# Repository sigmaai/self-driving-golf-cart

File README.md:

<center>

</center>

⚠️ This repo is no longer being maintained. Feel free to use the source or send me any questions, unfortunately no new commits or PRs will be added/accepted ⚠️

Welcome! This is an open source self-driving development platform aimed for rapid prototyping, deep learning, and robotics research. The system currently runs on a modified electric golf cart. Here are our goals:

### Goals:
Research and develop a deep learning-driven self-driving car. The vehicle should be able to achieve level 4 autonomy within a geofenced area.

#### The modules in this project.

1. End-to-End Steering (Behavioral cloning)
2. Semantic Segmentation
3. Object Detection 🚙
4. Drive by Wire (DBW)
5. CARLA simulator integration 
6. ZED stereoscopic vision system
7. Mapping with rtabamp
8. Path planning with ROS nav stack. 
9. Localization, pose tracking, and odom with ZED and rtabmap.

For the full documentation of the development process, please visit my website: [www.neilnie.com](https://www.neilnie.com)

## Table of Content
- [Try it out](#Try%20it%20out)
- [About ROS](./ros/README.md)
- [Simulation](#Simulation)
- [Autopilot & End-to-End Behavioral Cloning](./ros/src/autopilot/README.md)
- [Semantic Segmentation](./ros/src/segmentation/README.md)
- [The Navigation Stack](./ros/src/navigation/README.md)

## Try it out
Before you jump in, let me describe the hardware requirement for this project. **A webcam is the minimum requirment.** At this point, you can only run the whole system on the actual self-driving vehicle. ROS will throw warnings (even errors) at you if you don't have the hardware connected to your Linux machine. **If you don't have access to the hardware setup, don't worry** 👇
 
- The best way is to download and play back the ROS bags. [coming soon...]
- You can tryout individual packages and nodes, and might find them helpful for your own projects. 
- You can also tryout the CARLA simulator. (Maybe even improve the current system.)

To compile the project:

##### Requirements

1. Make sure that you have [ROS](http://wiki.ros.org/melodic/Installation/Ubuntu) installed on your computer. (I am using ROS Melodic)
2. Make sure you have all the [dependencies](./ros/requirements.txt) installed. 

##### Clone & Compile

1. Clone the repository. `$ git clone https://github.com/sigmaai/self-driving-golf-cart.git`
2. `$ cd self-driving-golf-cart/ros` 
3. `$ catkin_make`
4. `$ source devel/setup.bash`

##### Launch ZED cameras
- `$ roslaunch zed_wrapper zed.launch` (no rviz)
- `$ roslaunch zed_display display.launch` (with rviz)

##### Launch the Navigation Stack
- `$ roslaunch path_planning rtab_mapping_navigation.launch` 

<center>
	
</center>

🚙 Bon Voyage 😀

# Contact / Info
If you are interested in the detailed development process of this project, you can visit Neil's blog at [neilnie.com](https://neilnie.com) to find out more about it. Neil will make sure to keep you posted about all of the latest development on the club.

**Developers:**

**Neil (Yongyang) Nie** | [Email](mailto:yongyang.nie@gmail.com) | [Github](https://www.github.com/NeilNie) | [Website](neilnie.com) | [Linkedin](https://www.linkedin.com/in/yongyang-neil-nie-896204118/)

**Michael Meng** | [Email](mailto:xmeng18@deerfield.edu) | [Github](https://github.com/xmeng17)

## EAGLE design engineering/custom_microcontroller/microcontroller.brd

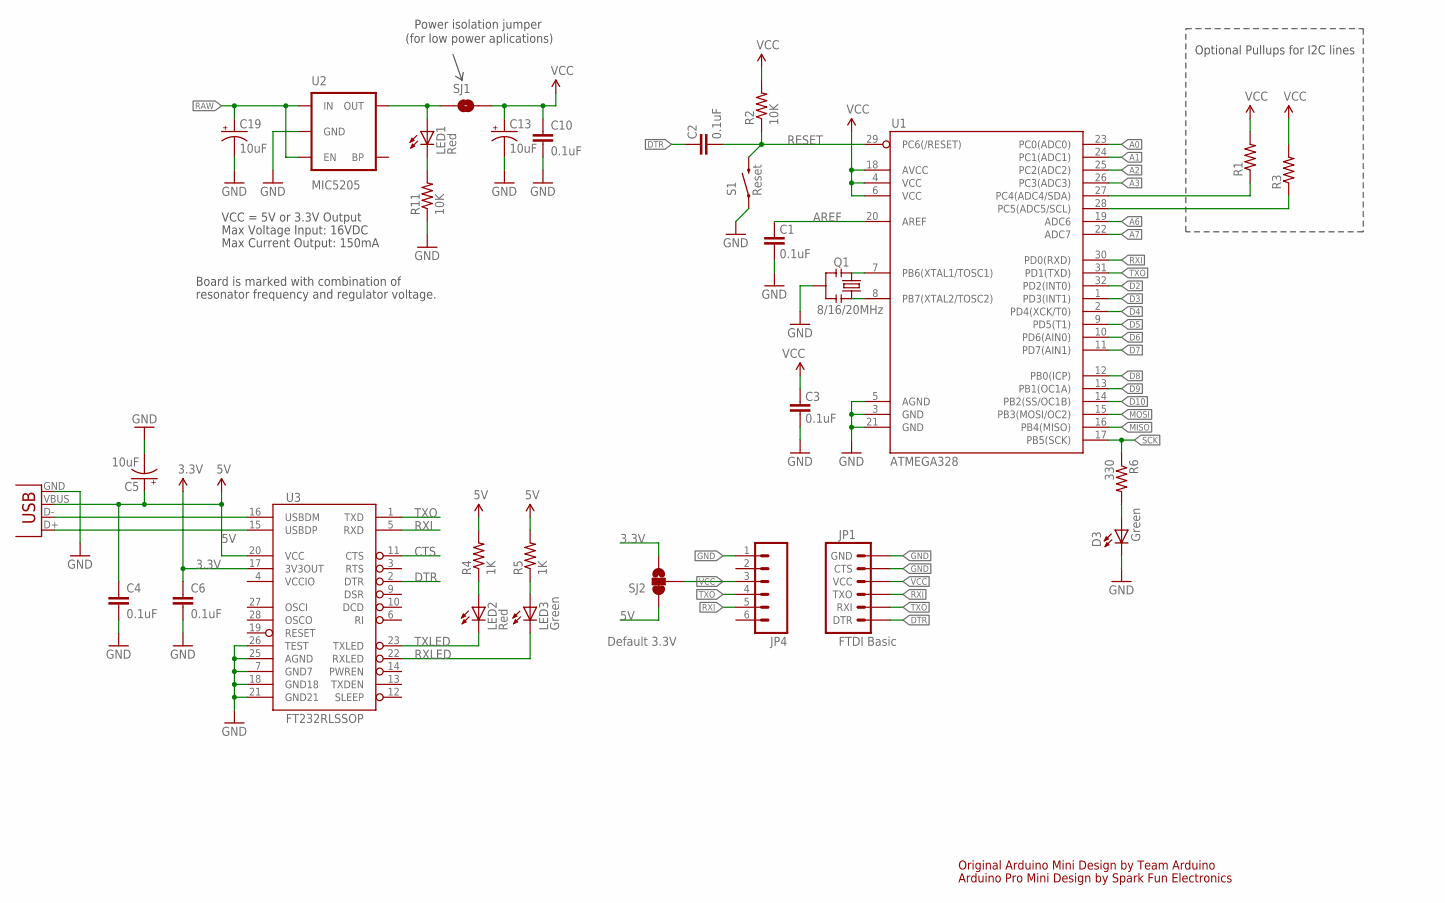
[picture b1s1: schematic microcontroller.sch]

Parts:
C1, C2, C3, C10: 0.1uF; 0603-CAP
C4, C6: 0.1uF; 0402-CAP
C5, C13, C19: 10uF; EIA3216
D3: Green; 0603-LED-ALT1
JP1: FTDI Basic; 1X06
JP4: M06SMD-FEMALE-V2; 1X06-SMD-FEMALE-V2
LED1: Red; 0603-LED-ALT1
LED2: Red; LED-0603
LED3: Green; LED-0603
Q1: 8/16/20MHz; RESONATOR-SMD-1:1
R1, R3: RESISTOR0603-RES; 0603-RES
R2, R11: 10K; 0603-RES
R4, R5: 1K; 0402-RES
R6: 330; 0603-RES
S1: Reset; TACTILE-SWITCH-SMD-ALT01
SJ1: SOLDERJUMPERNC; SJ_2S
SJ2: SOLDERJUMPER_2WAYS; SJ_3
U1: ATMEGA328; TQFP32-08
U2: MIC5205; SOT23-5
U3: FT232RLSSOP; SSOP28DB
X2: USB-SMD-NS; USB-MINIB-NOSTOP

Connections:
3.3V: C6.1, SJ2.3, U3.17 (3V3OUT)
5V: C4.1, C5.A (+), R4.2, R5.2, SJ2.1, U3.20 (VCC), X2.VBUS
A0: U1.23 (PC0(ADC0))
A1: U1.24 (PC1(ADC1))
A2: U1.25 (PC2(ADC2))
A3: U1.26 (PC3(ADC3))
A4: R1.1, U1.27 (PC4(ADC4/SDA)); also elsewhere on the board
A5: R3.1, U1.28 (PC5(ADC5/SCL)); also elsewhere on the board
A6: U1.19 (ADC6); also elsewhere on the board
A7: U1.22 (ADC7); also elsewhere on the board
AREF: C1.2, U1.20 (AREF)
CTS: JP4.2, U3.11 (CTS)
D2: U1.32 (PD2(INT0)); also elsewhere on the board
D3: U1.1 (PD3(INT1)); also elsewhere on the board
D4: U1.2 (PD4(XCK/T0)); also elsewhere on the board
D5: U1.9 (PD5(T1)); also elsewhere on the board
D6: U1.10 (PD6(AIN0)); also elsewhere on the board
D7: U1.11 (PD7(AIN1)); also elsewhere on the board
D8: U1.12 (PB0(ICP)); also elsewhere on the board
D9: U1.13 (PB1(OC1A)); also elsewhere on the board
D10: U1.14 (PB2(SS/OC1B))
DTR: C2.2, JP1.1 (DTR), JP4.6, U3.2 (DTR)
GND: C1.1, C3.1, C4.2, C5.C (-), C6.2, C10.2, C13.C (-), C19.C (-), D3.C, JP1.5 (CTS), JP1.6 (GND), JP4.1, Q1.2, R11.1, S1.1, S1.2 (1), U1.3 (GND), U1.5 (AGND), U1.21 (GND), U2.2 (GND), U3.7 (GND7), U3.18 (GND18), U3.21 (GND21), U3.25 (AGND), U3.26 (TEST), X2.GND; also elsewhere on the board
MISO: U1.16 (PB4(MISO))
MOSI: U1.15 (PB3(MOSI/OC2))
unnamed: Q1.3, U1.8 (PB7(XTAL2/TOSC2))
unnamed: Q1.1, U1.7 (PB6(XTAL1/TOSC1))
unnamed: LED1.A, SJ1.1, U2.5 (OUT)
unnamed: LED1.C, R11.2
unnamed: LED2.A, R4.1
unnamed: LED3.A, R5.1
unnamed: D3.A, R6.2
RAW: C19.A (+), U2.1 (IN), U2.3 (EN)
RXI: JP1.3 (TXO), JP4.5, U1.30 (PD0(RXD)), U3.5 (RXD); also elsewhere on the board
RXLED: LED3.C, U3.22 (RXLED)
SCK: R6.1, U1.17 (PB5(SCK))
TXLED: LED2.C, U3.23 (TXLED)
TXO: JP1.2 (RXI), JP4.4, U1.31 (PD1(TXD)), U3.1 (TXD); also elsewhere on the board
USB_D+: U3.15 (USBDP), X2.D+
USB_D-: U3.16 (USBDM), X2.D-
VCCIO: U3.4 (VCCIO)

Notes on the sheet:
Original Arduino Mini Design by Team Arduino
Arduino Pro Mini Design by Spark Fun Electronics
Max Voltage Input: 16VDC
Max Current Output: 150mA
Board is marked with combination of
resonator frequency and regulator voltage.
VCC = 5V or 3.3V Output
Optional Pullups for I2C lines
Power isolation jumper
(for low power aplications)
Default 3.3V

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
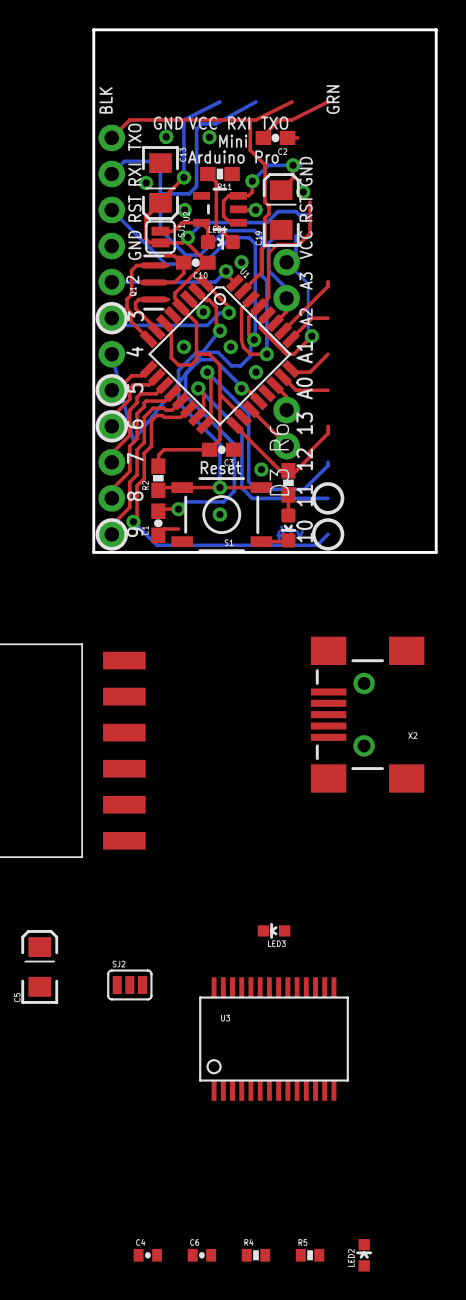
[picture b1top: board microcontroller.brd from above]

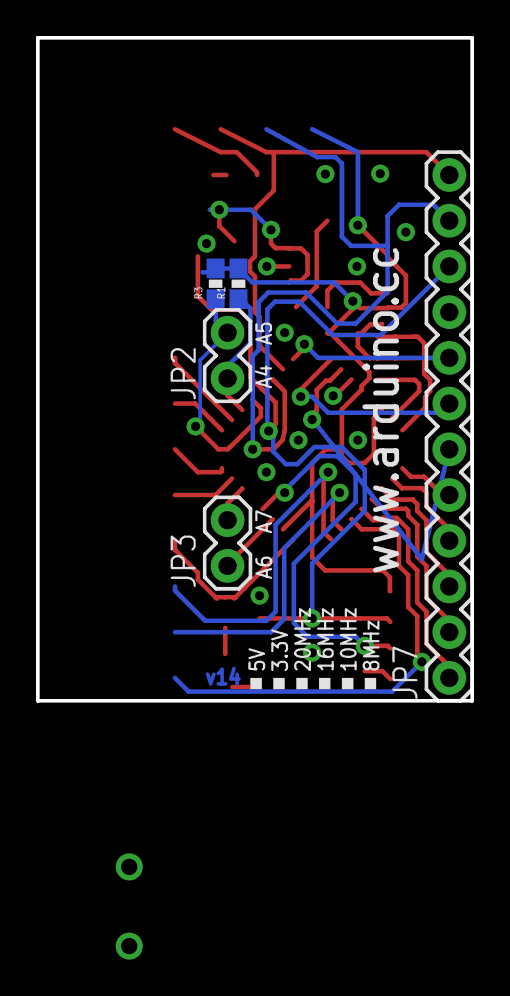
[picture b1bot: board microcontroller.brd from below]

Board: 2 copper layers, 24.1 x 36.8 mm, 32 parts (5 on the bottom side), 36 nets.

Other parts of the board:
JP2, JP3: 1X02
JP7: 1X12

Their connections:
A4: JP2.1; also elsewhere on the board
A5: JP2.2; also elsewhere on the board
A6: JP3.1; also elsewhere on the board
A7: JP3.2; also elsewhere on the board
D2: JP7.8; also elsewhere on the board
D3: JP7.7; also elsewhere on the board
D4: JP7.6; also elsewhere on the board
D5: JP7.5; also elsewhere on the board
D6: JP7.4; also elsewhere on the board
D7: JP7.3; also elsewhere on the board
D8: JP7.2; also elsewhere on the board
D9: JP7.1; also elsewhere on the board
GND: JP7.9; also elsewhere on the board
RXI: JP7.11; also elsewhere on the board
TXO: JP7.12; also elsewhere on the board

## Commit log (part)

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2017-10-25 newly trained files
2017-10-27 new error function added
2017-10-30 directory changed & small changes
2017-10-31 steering training modifications
2017-11-01 merging method finished
2017-11-04 attempted to make vechicle detection work
2017-11-09 ready for training uolo
2017-11-16 engineering files added & egpu set completed
2017-11-21 segmatation keras training improvements
2017-11-29 directory changed
2017-12-01 steering visualization works, lane detection added, traffic signal added
2017-12-03 servo code 'actually' added
2017-12-08 google maps & segmentation works
2017-12-20 MultiNet removed, begin implementing SegNet
2017-12-23 cruse added & other small changes
2018-01-06 round steering angle
2018-01-09 update arduino
2018-01-09 add case if does not get message
2018-01-10 motor integration
2018-01-12 fixed state
2018-01-14 schematics & engineering
2018-01-17 used new motor controller to handle higher amp
2018-01-23 cruse control code added
    - arduino serial python code added
    - speed predictor class added
    Note: need more training
    (same with steering)
2018-01-24 added two way communications
2018-01-25 cruse & steering training files changes
2018-01-30 latest training changes
2018-01-31 spelling error corrected
2018-02-05 small changes
2018-02-08 many changes
    - segmentation comfirmed to be working
    - segmentation visualization file updated
    - segmentation integrated into drive.py
    - drive.py detector stuff removed
    - vehicle detector dir removed
    - changed printing color for drive.py
2018-02-09 latest changes to be pushed to cart
2018-02-11 small changes
    pretty much meaningless
2018-02-14 small changes on cruise control
2018-02-20 arduino code updated, ready for some testing
2018-02-23 changes on cart
2018-02-25 tried rambo, didn't really work
2018-02-26 AutoPilot added, see if it works.
2018-03-01 multi-camera implemented & other small changes
2018-03-02 readme and other small changes
2018-03-06 data set collector implementations
2018-03-08 Updated license
2018-03-25 small changes & data set preprocessing
2018-04-05 detection stuff added 🚘
    - Yolo v2 added (again)
    - Lane detector added
    - traffic light detector added
2018-04-08 updated README
    and other small changes
2018-04-10 steering visualization changes
2018-04-11 important changes to visualization 😎
    1. info screen implemented
    2. changes to driver class
    3. driving visualization updates
    3. removed some todos
    4. small things
2018-04-12 tested & verified latested changes on vehicle computer
2018-04-18 some major UI changes
2018-04-22 created a catkin workspace for logger. Created a ROS node called steering_logger
2018-04-23 small changes to master
2018-04-23 ros branch initial commit 🤖
2018-04-24 logger implementation ready to test
2018-04-25 steering publisher finally works!
2018-04-28 steering wheel mesh added, steering visualization node implemented & tested
2018-04-30 implemented some detection stuff
2018-05-02 dataset preprocessinng & steering module reorganized
2018-05-05 small doc changes.
2018-05-07 basic gps localization implementations
2018-05-09 steer train script changes & others
2018-05-14 updated readme & steering training scripts
2018-05-18 begin training on new dataset
2018-05-20 localization initial commit
2018-05-22 particle filter implementation finished
2018-05-25 updated some documentations
2018-05-26 steering testing script added
2018-06-01 training with ConvLSTM seems to be working!
2018-06-05 lots of failed training / validation attempts
2018-06-19 removing ml experiment
2018-07-11 merging commits
2018-08-05 new steering node works
    1. be aware of image publisher name bug.
    2. perhaps write in more warning
2018-09-12 integrated yolo detection to ros
2018-11-03 working on converting detection from yolo 2 to 3
2018-11-10 yolov3 mostly added. encountered CuDNN issue
2018-11-18 experiment with travis
2018-11-21 segmentation msg added
2018-11-24 cruise control added. More testing needed.
2018-11-24 cruise controrol visualization added. Need to look into GPU useage stuff
2018-11-26 autopilot added, replacing steering and cruise control
2018-12-18 README updated, cleaned up
2018-12-23 important small documentary updates
    - rewrote readme for ros.
    - updated some script headers.
    - other small changes.
2018-12-27 codebeat badge added to readme
2018-12-30 joystick package added
2019-01-06 joystick enabled arduino code added
    not tested
2019-01-07 joystick linear actuator control added, successful
2019-01-09 linear actuator min max bug fixed
2019-01-10 segmentation node fixed, working
    - after adding ICNet, fixed the ROS stuff.
2019-01-17 segmentation changes
2019-01-20 joystick accelerator control finished, tested
2019-01-24 media content updated
2019-01-29 simulation script
    - simulation conversion script added
    - attempt to decrease reliance on config.py
    - * need to implement simulation camera select
2019-02-01 segmentation fixed, improved camera input select
    - camera input select node created (nested in the cv_camera package)
    * now, all systems subscribes to '/vehicle/sensor/camera/front/image_color'
    switch camera input source using [start] & [A] button
    - semantic segmentation bug fixed. removed some previously added features. now the visualization has the proper ratio
    notes:
    - make the segmentation code more generalized.
2019-02-05 ROS bridge source added to project
    installing rosbridge locally using apt-get gave me errors when using launch file.
2019-02-15 Kitti image tools added, not working.
2019-03-25 removed some experimentary nodes
2019-03-29 zed integrated into the segmentation system
    - ZED sensor packages added.
    (ZED config modified)
    - FusionNet added.
    - segmentation_node modified for depth map
    - new frame rate ~16fps
    - other small changes.
2019-04-01 PCL experiments
    - Voxel filter working
    - camera initial position issues
    - point cloud not transformed
    - plane segmentation not functioning well
2019-04-03 segmentation to birds eye view working
    - need to integrate that into ROS
    - need to figure out point cloud ground detection
    - test the RGB segmentation
    * summarize this week's progress (maybe next commit)
2019-04-06 rgb segmentation -> point cloud road data
    important update:
    - rgb ConvNet segmentation result now can be directly converted to point cloud data. This is critical for rgb and PCL fusion
    - segmentation now publishes a new topic /segmentation/output/road
    - added new node, rgb_segmentation_point_cloud. this node subscribes to the segmentation output, and then loop through the image. While looping, it picks out pixels that have been classified as road.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
    - other small changes
2019-04-08 minor documentation changes
    - in previous commit, also changed some node names, because there were multiple nodes with the same name.
    - also, pay attention to the transform_point_cloud node, this node might be useless.
2019-04-10 very rough path planning with rtab and actionlib
    - visual based slam with rtab
    - goal publishing with actionlib
    - navigation stack.
2019-04-15 able to resize global gridmap, however, unable to construct accurate global map
    1. map expansion works.
    2. however, the expansion doesn't take into account the heading of the vehicle. Therefore, the map constructed isn't accurate.
    3. Path planning seems to be kinda working. However, because there is no accuracy global map, path planning doesn't work just yet.
2019-04-18 attempt to decrease computation time, small modifications
    - hybrid a star planner issue identified, the start and finish must be located in free space. Therefore, must implement dynamic start and goal.
    - takes around 0.3 sec to construct map, takes 0.3 to segment point cloud. try to decrease that time.
    problems:
    - global navigation goal broadcast has issues.
    - try to add behavioral cloning back to the system.
    - test behavioral cloning.
2019-04-21 point cloud -> laser integrated to rtabmap
    - the point cloud -> laser scan package seems to help rtabmap to obtain an accurate map.
    Notes:
    1. must test drive and test new flat camera dataset. Somehow, ROS tf gitters.
    2. Figure out what's wrong with the local map. Why local map not sure
    3. Re do the path planner yaml file. Sometimes the global map goes through obstacles.
2019-04-23 successfully mapped environment, planned local & global path
    - optimized parameter files, especially the path planner file.
    - created one really good map of behind the koch center. Wait for a cloudy day and conduct more mapping.
    - turns out, path planner refresh rate, maps refresh rates are all good.
    - able to observe /cmd_vel output. seems reasonable. need arduino actuation implementation.
    - other small changes.
    Overall good progress. After some documentation changes, ready for pull request
2019-04-26 major navigation parameter optimizations
    - always clear param server when changing params
    - local planner params need to be tested (decrease lag)
    - local map add laser scan
    - local map add clearing point clouds
    - lots lots lots of testing and driving
    - removed some useless files.
2019-04-30 added segmentation to local costmap sensor array
    unable to verify the effectiveness of the segmentation system.
2019-05-02 added new launch files for navigation, cleaned up useless files
    - now three launch files for rtabmap
    1. mapping only
    2. publish grid map, localization, odom, publish tf
    3. publish grid map. no local, no odom, no tf
    - two launch files for path planning.
    1. uses odom from zed
2019-05-03 removed deprecated packages for stable release
2019-05-07 kill switch code added
2019-05-08 RC braking, accelerator, steering all working, tested
2019-05-16 ROS <--> iOS improvements
    - tested navigation goal publisher
    - updated some parameters in costmap
    - updated some parameters in planner
    - still need to test and improve the pose updater.
    - web socket added to project.
    - steering visualization node added to the joystick control launch file.
2019-09-29 some minor changes for final testing
2019-12-16 Bump tensorflow-gpu from 1.13.1 to 1.15.0 in /ros
    Bumps [tensorflow-gpu](https://github.com/tensorflow/tensorflow) from 1.13.1 to 1.15.0.
    - [Release notes](https://github.com/tensorflow/tensorflow/releases)
    - [Changelog](https://github.com/tensorflow/tensorflow/blob/master/RELEASE.md)
    - [Commits](https://github.com/tensorflow/tensorflow/compare/v1.13.1...v1.15.0)
2020-03-27 cleaning up
2020-11-06 Bump pillow from 6.2.0 to 7.1.0 in /ros
    Bumps [pillow](https://github.com/python-pillow/Pillow) from 6.2.0 to 7.1.0.
    - [Release notes](https://github.com/python-pillow/Pillow/releases)
    - [Changelog](https://github.com/python-pillow/Pillow/blob/master/CHANGES.rst)
    - [Commits](https://github.com/python-pillow/Pillow/compare/6.2.0...7.1.0)
2021-08-25 Bump tensorflow-gpu from 1.15.4 to 2.5.1 in /ros
    Bumps [tensorflow-gpu](https://github.com/tensorflow/tensorflow) from 1.15.4 to 2.5.1.
    - [Release notes](https://github.com/tensorflow/tensorflow/releases)
    - [Changelog](https://github.com/tensorflow/tensorflow/blob/master/RELEASE.md)
    - [Commits](https://github.com/tensorflow/tensorflow/compare/v1.15.4...v2.5.1)
    ---
    updated-dependencies:

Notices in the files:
README.md:
License: MIT
parts and their libraries:
SparkFun-Passives: Licensing: CC v3.0 Share-Alike You are welcome to use this library for commercial purposes.
